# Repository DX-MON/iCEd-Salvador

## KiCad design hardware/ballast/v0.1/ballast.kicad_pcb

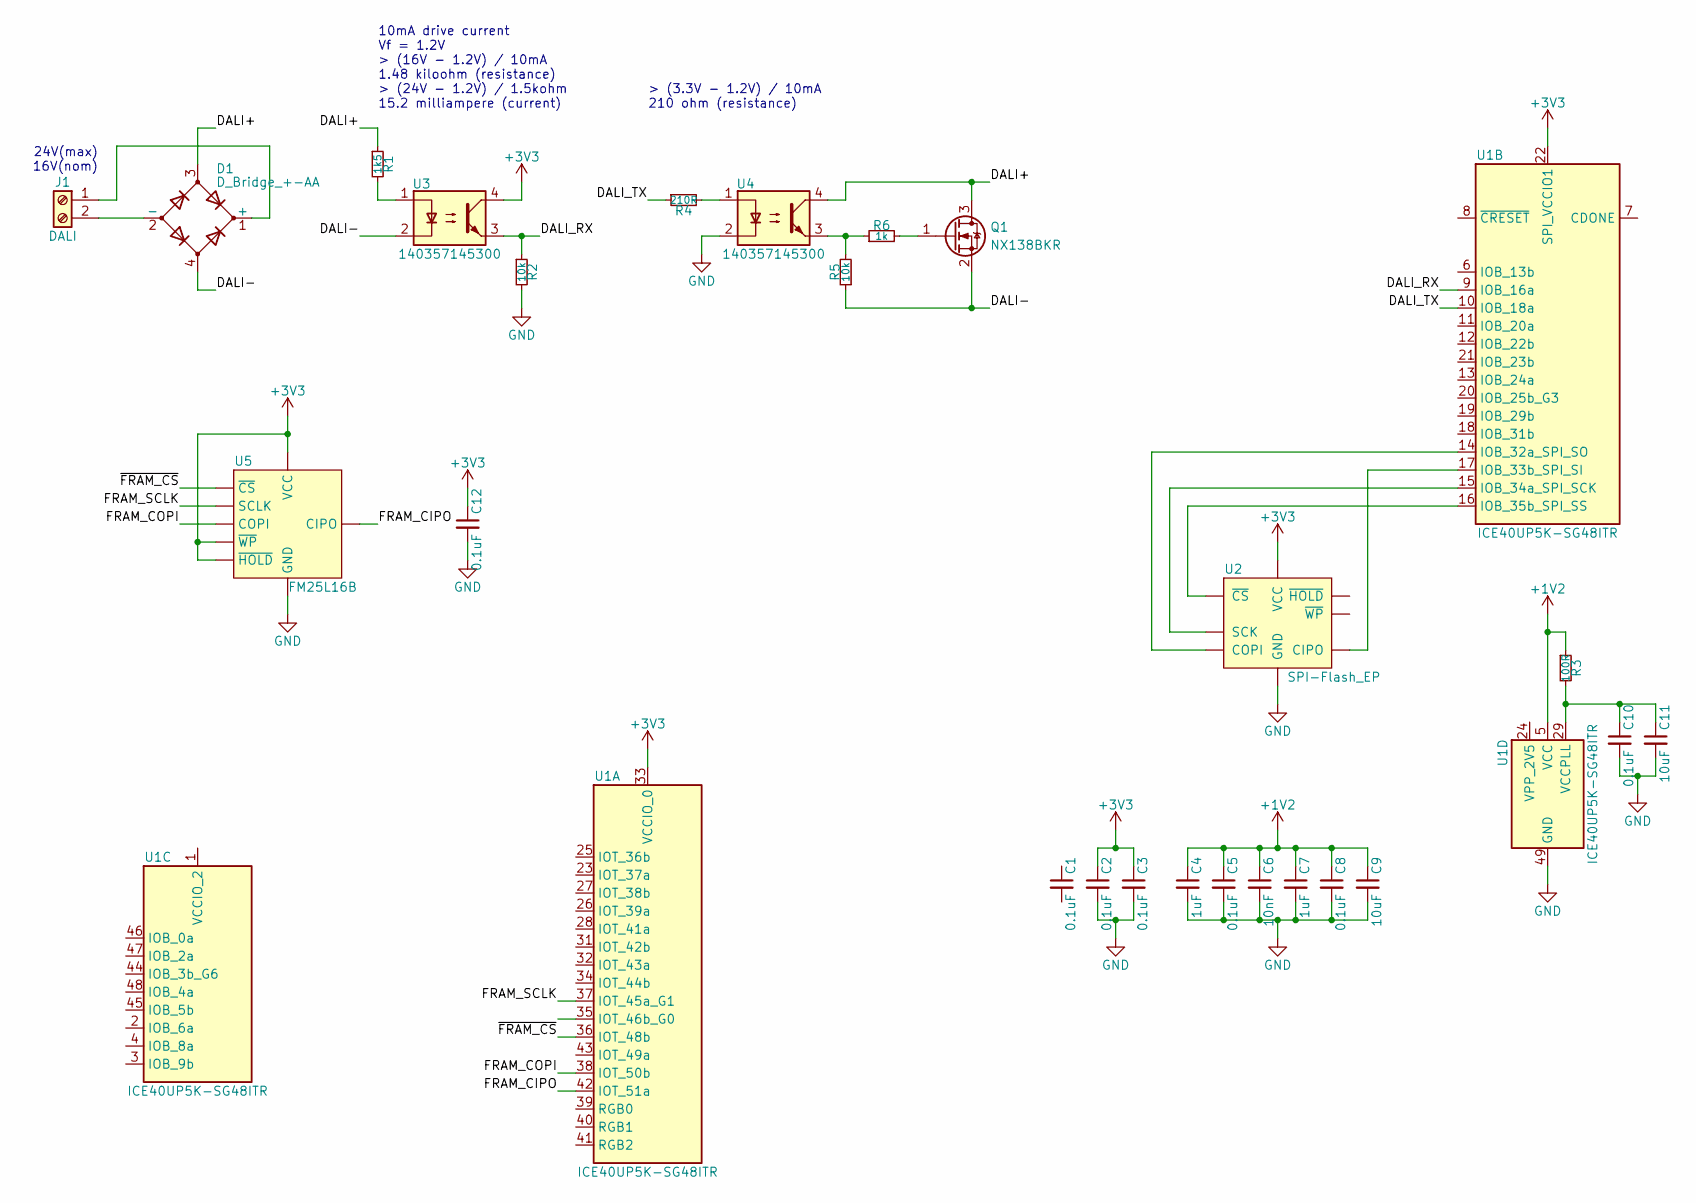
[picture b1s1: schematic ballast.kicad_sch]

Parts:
C1, C2, C3, C5, C8, C10, C12: 0.1uF; C0603
C4, C7: 1uF; C0603
C6: 10nF; C0603
C9, C11: 10uF; C0603
D1: D_Bridge_+-AA; Bridge_Bridge_DBL; MPN DBLS101G
J1: DALI; PhoenixContact_MSTBA_2,5_2-G-5,08_1x02_P5.08mm_Horizontal
Q1: NX138BKR; SOT-23; MPN NX138BKR
R1: 1k5; R0603
R2, R5: 10k; R0603
R3: 100R; R0603
R4: 210R; R0603
R6: 1k; R0603
U1: ICE40UP5K-SG48ITR; QFN-48-1EP_7x7mm_P0.5mm_EP5.6x5.6mm
U2: SPI-Flash_EP; UDFN-8-1EP_6x5mm_P1.27mm_EP3.4x4mm
U3, U4: 140357145300; SO-4_4.4x3.6mm_P2.54mm; MPN 140357145300
U5: FM25L16B; WDFN-8-1EP_4x4.5mm_P0.95mm_EP2.6x3.6mm

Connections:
+1V2: C4.1, C5.1, C6.1, C7.1, C8.1, C9.1, R3.1, U1.5 (VCC), U1.30 (VCC)
+3V3: C2.1, C3.1, C12.1, U1.22 (SPI_VCCIO1), U1.33 (VCCIO_0), U2.8 (VCC), U3.4, U5.3 (~WP), U5.7 (~HOLD), U5.8 (VCC)
/DALI+: D1.3, Q1.3 (D), R1.1, U4.4
/DALI-: D1.4, Q1.2 (S), R5.1, U3.2
/DALI_RX: R2.1, U1.9 (IOB_16a), U3.3
/DALI_TX: R4.1, U1.10 (IOB_18a)
/FRAM_CIPO: U1.42 (IOT_51a), U5.2 (CIPO)
/FRAM_COPI: U1.38 (IOT_50b), U5.5 (COPI)
/FRAM_SCLK: U1.37 (IOT_45a_G1), U5.6 (SCLK)
/~FRAM_CS: U1.36 (IOT_48b), U5.1 (~CS)
GND: C2.2, C3.2, C4.2, C5.2, C6.2, C7.2, C8.2, C9.2, C10.2, C11.2, C12.2, R2.2, U1.49 (GND), U2.4 (GND), U2.9 (GND), U4.2, U5.4 (GND)
unnamed: C10.1, C11.1, R3.2, U1.29 (VCCPLL)
unnamed: D1.1 (+), J1.1
unnamed: D1.2 (-), J1.2
unnamed: Q1.1 (G), R6.2
unnamed: R1.2, U3.1
unnamed: R4.2, U4.1
unnamed: R5.2, R6.1, U4.3
unnamed: U1.14 (IOB_32a_SPI_SO), U2.5 (COPI)
unnamed: U1.15 (IOB_34a_SPI_SCK), U2.6 (SCK)
unnamed: U1.16 (IOB_35b_SPI_SS), U2.1 (~CS)
unnamed: U1.17 (IOB_33b_SPI_SI), U2.2 (CIPO)

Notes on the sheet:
24V(max) 16V(nom)
10mA drive current Vf = 1.2V > (16V - 1.2V) / 10mA 1.48 kiloohm (resistance) > (24V - 1.2V) / 1.5kohm 15.2 milliampere (current)
> (3.3V - 1.2V) / 10mA 210 ohm (resistance)

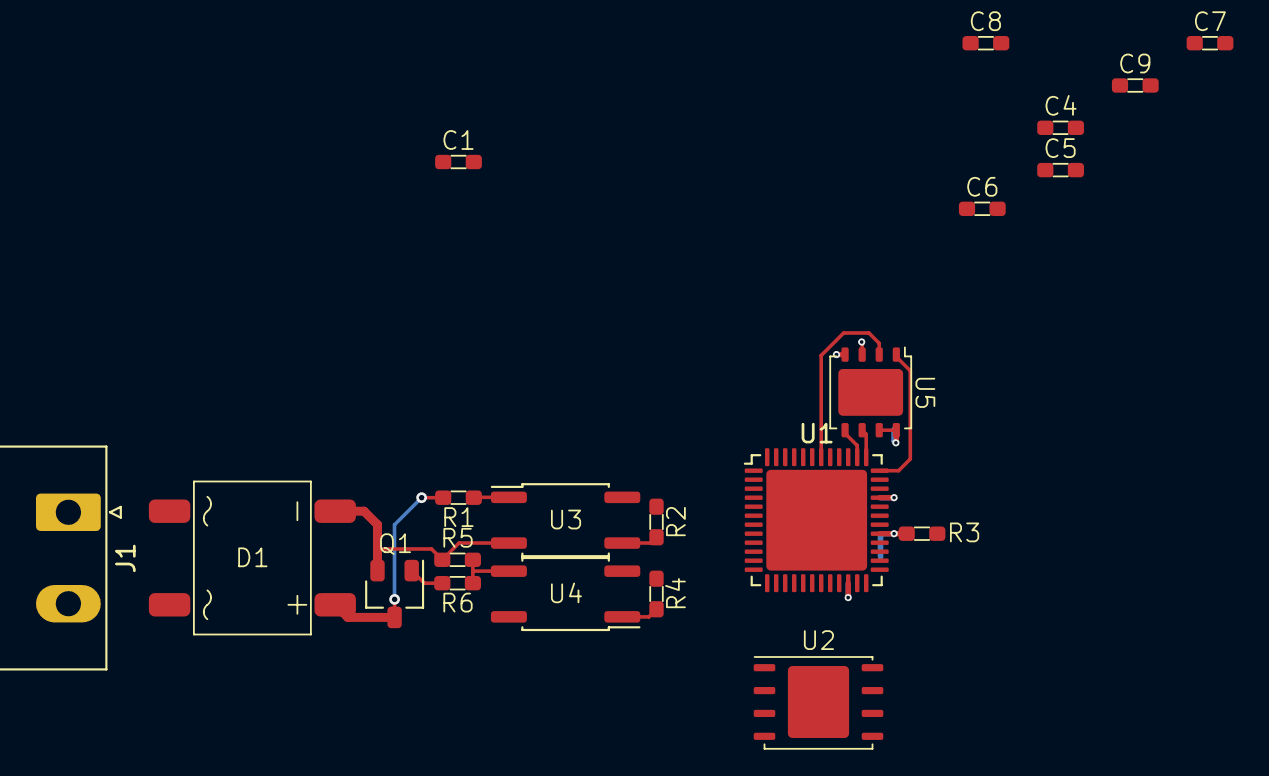
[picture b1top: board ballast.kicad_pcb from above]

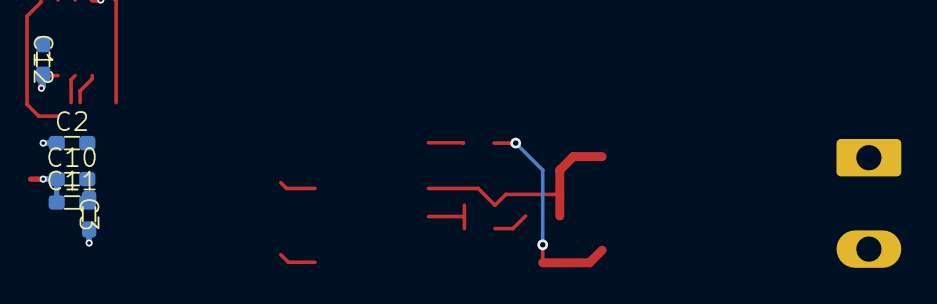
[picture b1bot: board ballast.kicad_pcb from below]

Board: 4 copper layers, 26 parts (5 on the bottom side), 22 nets.

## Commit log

2021-08-28 Added a license and code of conduct for the project
2021-08-28 Added stubs for the nMigen gateware
2021-08-28 Started a stub for the gateware platform for the project
2021-09-12 Added some sanity ignores
2021-09-12 Implemented a Manchester encoder/decoder with bypass
2021-09-12 Implemented the receive part of the DALI transceiver
2021-09-12 Defined a DALI resource and added it and the clock to the platform
2021-09-12 Added gateware for implementing DALI protocol handling and the project top-level gateware
2021-09-12 Implemented a runner for the gateware build process
2021-09-12 Implemented a sim to test the RX part of the DALI serial interface gateware
2021-09-12 Implemented a sim runner for the gateware
2021-09-12 Begun designing the PCB for the project
2021-09-17 Switched the sim runner over to Arachne's now it works right
2021-09-18 Renamed all the receive related signals in the serial component for DALI to deconflict with transmit
2021-09-18 Implemented DALI transmit serialisation
2021-09-18 Implemented a test bench for the new DALI TX functionality
2021-09-18 Created the decoder for the base DALI command set
2021-09-18 Created the decoder for the LED-specific command set
2021-09-18 Plummed the new decoder into the DALI submodule tree
2021-09-18 Added nop commands and finished decoding data-in-command stuff out
2021-09-19 Added a send complete signal to the DALI serial interface
2021-09-19 Begun implementing the DALI command handling
2021-09-19 Fixed the data that has been read in not getting assigned to the serial module dataOut signal
2021-09-19 Fixed a couple of issues that prevented the DALI submodule properly synthesising
2021-09-19 Implemented a sim for the DALI top-level state machine
2021-09-19 Fixed a oopsie with the Manchester decoder bypass
2021-09-19 Added documentation to the serial RX state machine
2021-09-19 Documented the tx serial state machine
2021-10-02 Begun fleshing out the main state machine
2021-10-02 Refactored out the repeated register to DALI writeback into a function
2021-10-02 Implemented the first batch of store commands These need some kind of backing storage (FRAM) as they need to be persistent
2021-10-03 Implemented support for SPI-connected FRAM
2021-10-03 Naming consistency for the failureLevel register stuff
2021-10-03 Added a SPI resource for the FRAM
2021-10-03 Implemented FRAM-based writeback of many of the DALI registers
2021-10-03 Implemented add/remove group and dtr -> shortAddress
2021-10-03 Implemented serveral status items
2021-10-03 Added the FRAM for persisting DALI config to the board
2021-10-03 Fixed a couple of issues found during simulation of the FRAM SPI bus
2021-10-03 Added a simulation for the FRAM SPI bus
2021-10-03 Adjusted the DALI sim to take into account the FRAM interface
2021-10-03 Implemented a sim for the FRAM controller core
2021-10-03 Fixed a bug with overlapped start-finish in the FRAM bus controller
2021-10-03 Cleaned up the ~cs line generation for the FRAM to open the timings up a little
2021-10-03 Fixed the COPI output enabel not being put back high at the end of a read cycle
2021-10-04 Implemented DALI address decoding and the first of the special commands
2021-10-04 Begun implementing a test for the DALI levels commands
2021-10-04 Added some initial testing for addressing
2021-10-23 Implemented startup read out of the persisted device state
2021-10-23 Fixed the name of the scene signals
2021-10-23 Added simulation for the startup read out in the DALI core
2021-10-23 Added writeback for the other registers that are written to FRAM
2021-10-23 Added provisional support for the queryShortAddress special command
2021-10-24 Fixed a bug in the DALI sim due to timebase issues
2021-10-24 Added a action for generating the sim RTL for sim.dali.dali.readStartup
2021-10-24 Added the cxxrtl-based version of sim.dali.dali.startupRead
2021-12-22 Fixed up the top-level .gitignore now the virtual environment is named 'env'
